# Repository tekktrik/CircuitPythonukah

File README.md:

# CircuitPythonukiah Hardware

Hardware required for the [CircuitPythonukiah project](https://github.com/tekktrik/CircuitPythonukiah)

## Hardware Dependencies
Here are all the things needed: to physically build your very own CircuitPythonukiah:

### Custom Components

The project makes use of two custom parts. The first is the custom PCB that is the heart
of the CircuitPythonukiah.  The second is a base that can be 3D printed, which holds the
PCB upright.  You can find the PCB KiCAD design and fabrication files in the
`electrical/` folder, and you can find both the PCB's STEP file representation, as well
as the STEP and STL files for the base in the `mechanical/` folder.

### Mechanical (Off-The-Shelf)

This project uses the following off-the-shelf mechanical components:

* [Self-Tapping M5 Screw](https://www.mcmaster.com/90380A392/) (x1)
* [M5 Spacer](https://www.mcmaster.com/7298N112/) (x1)

### Electronics (Off-The-Shelf)
This project uses the following off-the-shelf electronic components:

* [QT Py ESP32-S2 Dev Board](https://www.adafruit.com/product/5325) (x1)
* [Piezo Buzzer](https://www.adafruit.com/product/160) (x1)
* [Slide Switch](https://www.digikey.com/en/products/detail/e-switch/EG1218/101726)
* [Super Bright Yellow 5mm LED](https://www.adafruit.com/product/2700>) (x9)
* [100 Ohm Resistor](https://www.digikey.com/en/products/detail/yageo/CFR-25JB-52-100R/246) (x9)
* [Male Header Pins (7 position)](https://www.digikey.com/en/products/detail/harwin-inc/M20-9770746/3727778) (x2)
* [Female Header Pins (7 position)](https://www.digikey.com/en/products/detail/sullins-connector-solutions/PPPC071LFBN-RC/810179) (x2)
* [USB C Receptacle](https://www.digikey.com/en/products/detail/cui-devices/UJC-VP-3-SMT-TR/14310511) (x1)

## Building Hardware

### Fabricating the Custom Components

There isn't necessarily one way to do this, but I can mention how I did it:

I used [JLCPCB](https://jlcpcb.com/) to fabricate my boards, mostly because I knew
they could do blue PCBs and the quote for the weirdly shaped PCB was better than
others I had looked at.

For the base, I used 0.2 mm layer thickness and 20% infill.  I also didn't use supports
when I printed since it came out pretty well without them, and I had a lot of trouble
removing the breakway supports otherwise.  I'm leaving it up to [Hubs](https://www.hubs.com/)
(the printing service I'll be using) to figure that last bit out (not sure I can specify
either).  I decided to print this in black rather than blue since the black made the
board "pop" more.

### Soldering the PCB

This is by far the most labor-intensive step.  Since I didn't plan on this being any
kind of big operation, I decided to hand-solder eerything to the board.  This was fairly
straight forward with the exception of a couple things:

* I would bend each LED so the pins so would be in just about the right place, and then I
  bend the wires again to somewhat lock it in place.  I'd then solder one pin to the board,
  while using one hand to hold the LED and PCB, and the other to use the soldering iron,
  which would allow me to remelt the solder and use my hand to finely position the LED.
* The USB C receptacle was a byproduct of not wanting multiple USB receptacle types
  between the microcontroller and the PCB.  I found that I could do a similar trick as
  the LED and solder one pad to "lock" it, and then use one hand to apply pressure while
  remelting the solder with the other.  Then I just applied solder across the pads, using
  some solder wick to get all the extra.

### Assembling Everything

I used a small hand tool to screw in the self-tapping screw, which helped make sure the board
wasn't rattling too much when everything is assembled.  Don't forget to add the spacer before
tightening everything!

## Licenses and Attribution

The hardware for this project is licensed under the CERN-OHL-S license, and uses components,
both original and modified, with the following licenses:

* Licensed under the Certification Mark License Agreement by the OSHWA:
  * Open Source Hardware Certification Mark
* Licensed under CC-SA by Macklin Chaffee:
  * Gear logo design
* Licensed under CC-BY-SA-4.0 with Design Exception 1.0 by SnapEDA:
  * [EG1218](https://www.snapeda.com/parts/EG1218/E-Switch/view-part/) (modified)
  * [UJC-VP-3-SMT-TR](https://www.snapeda.com/parts/UJC-VP-3-SMT-TR/CUI%20Devices/view-part)

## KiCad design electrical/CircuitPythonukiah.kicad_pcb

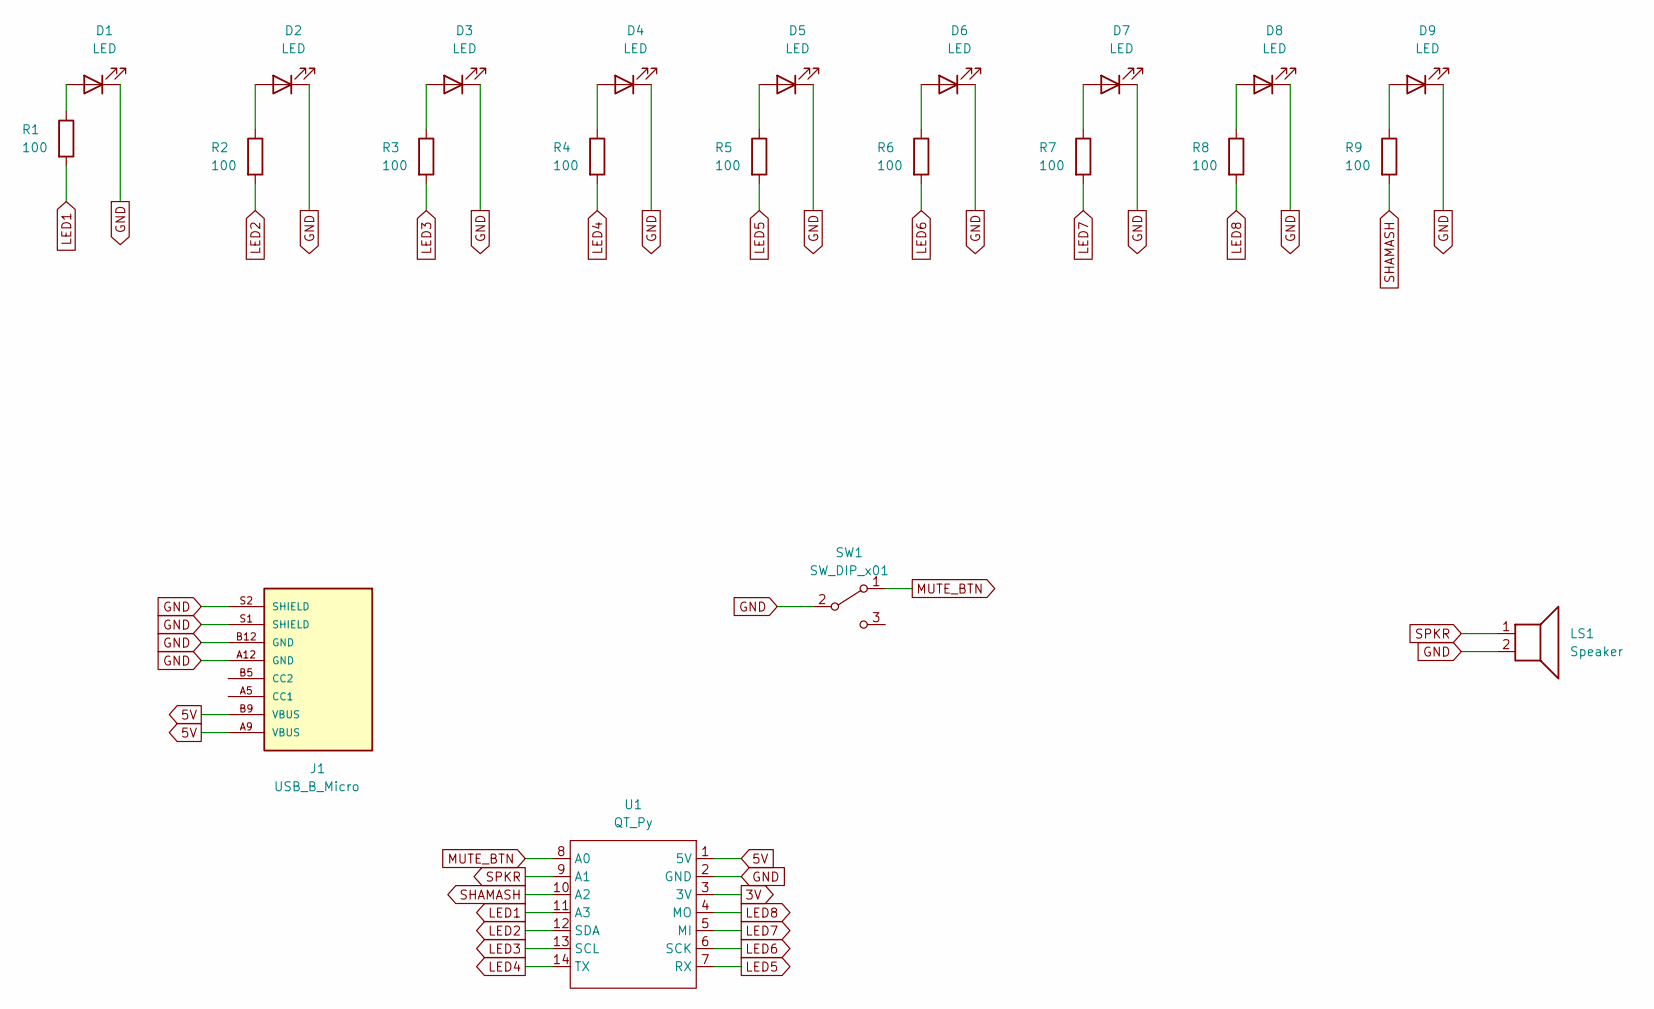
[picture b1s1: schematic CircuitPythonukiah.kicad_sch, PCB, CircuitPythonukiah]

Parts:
D1, D2, D3, D4, D5, D6, D7, D8, D9: LED; LED_D5.0mm_Horizontal_O6.35mm_Z3.0mm
J1: USB_B_Micro; CUI_UJC-VP-3-SMT-TR; PARTREV 1.0
LS1: Speaker; Piezo Buzzer
R1, R2, R3, R4, R5, R6, R7, R8, R9: 100; R_Axial_DIN0207_L6.3mm_D2.5mm_P7.62mm_Horizontal
SW1: SW_DIP_x01; EG1218; PARTREV May 20, 2003
U1: QT_Py; QT Py

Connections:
3V: U1.3 (3V)
5V: J1.A9 (VBUS), J1.B9 (VBUS), U1.1 (5V)
GND: D1.1 (K), D2.1 (K), D3.1 (K), D4.1 (K), D5.1 (K), D6.1 (K), D7.1 (K), D8.1 (K), D9.1 (K), J1.A12 (GND), J1.B12 (GND), J1.S1 (SHIELD), J1.S2 (SHIELD), LS1.2, SW1.2 (B), U1.2 (GND)
LED1: R1.2, U1.11 (A3)
LED2: R2.2, U1.12 (SDA)
LED3: R3.2, U1.13 (SCL)
LED4: R4.2, U1.14 (TX)
LED5: R5.2, U1.7 (RX)
LED6: R6.2, U1.6 (SCK)
LED7: R7.2, U1.5 (MI)
LED8: R8.2, U1.4 (MO)
MUTE_BTN: SW1.1 (A), U1.8 (A0)
unnamed: D1.2 (A), R1.1
unnamed: D2.2 (A), R2.1
unnamed: D3.2 (A), R3.1
unnamed: D4.2 (A), R4.1
unnamed: D5.2 (A), R5.1
unnamed: D6.2 (A), R6.1
unnamed: D7.2 (A), R7.1
unnamed: D8.2 (A), R8.1
unnamed: D9.2 (A), R9.1
SHAMASH: R9.2, U1.10 (A2)
SPKR: LS1.1, U1.9 (A1)

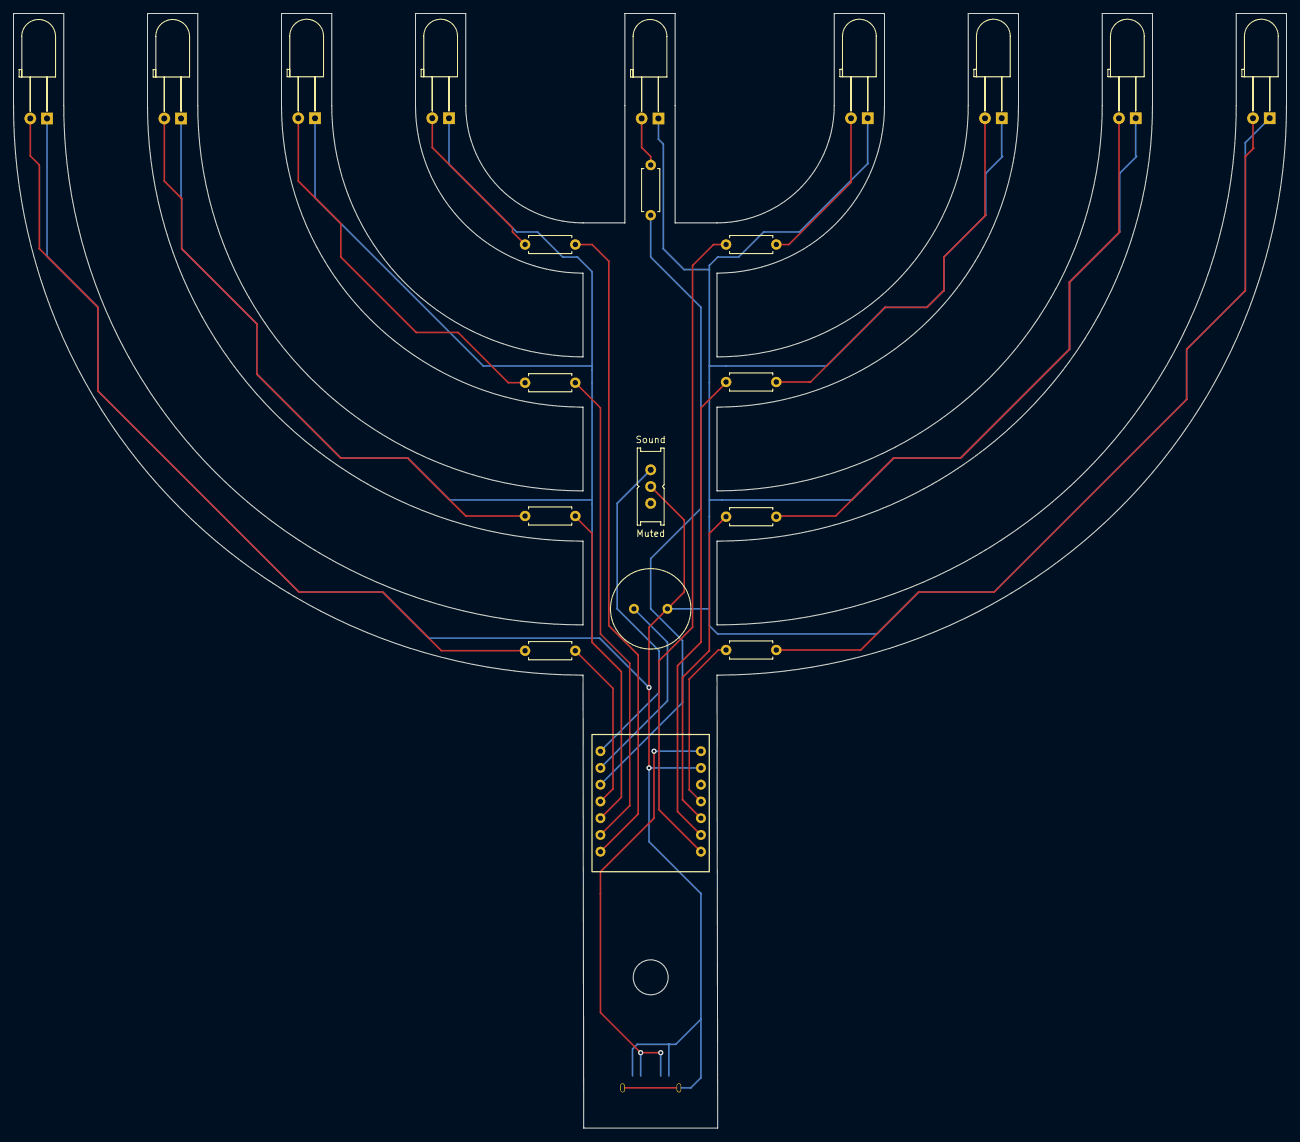
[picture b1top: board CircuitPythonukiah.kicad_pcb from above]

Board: 2 copper layers, 193.0 x 169.0 mm, 23 parts (1 on the bottom side), 22 nets.

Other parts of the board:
M5: MountingHole_5.3mm_M5

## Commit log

2022-04-30 Update project name in README
2022-04-30 Update .gitignore to ignore fabrication folder
2022-04-30 Add project files
2022-04-30 Update .gitignore to ignore backup folder
2022-04-30 Add symbol and footprints
2022-04-30 Add KiCAD files
2022-07-24 Update repo with currnt work
2022-08-14 Move USB-C to back side
2022-08-17 Flip microcontroller for ease of configuring
2022-08-27 Add STEP file output
2022-08-28 Regenerate fabrication outputs
2022-09-16 Change A0 to be pull-up input
2022-09-25 Update fabrication files
2022-10-05 Add preliminary hardware details
2022-10-05 Reorganize files
2022-10-05 Renamed PCB STEP file to pcb.step
2022-10-06 Prepare for pre-commit
2022-10-06 Reformatted STEP files
2022-10-06 Add licensing
2022-10-06 Add CI step for installing dependencies
2022-10-06 Make CI PR parent repo when main is updated
2022-10-06 Remove needs from update CI
2022-10-06 Reformatted per pre-commit
2022-10-06 Add minor fixes to README
2022-10-06 Minor fixes to README
2022-10-06 Fix update CI
2022-10-06 Minor README fixes
2022-10-06 Minor README fix
2022-10-06 Fix typo
2022-10-06 Fix title of README to reference hardware
2022-10-09 Update license to CERN OHL 2.0-S
2022-10-09 Update main license
2022-10-13 Add licenses for SnapEDA components
2022-10-13 Convert attribution to nested list
2022-10-14 Attribute gear logo
2022-10-14 Update PCB drawing info
2022-10-14 Update PCB schematic info
2022-10-14 Add dates as OCT12 to match OSHWA certification
2022-10-14 Add OSHWA mark to PCB
2022-10-14 Add OSHWA mark attribution in README
2022-10-14 Add badges
2022-10-14 Update wording in attribution
2022-10-14 Add CI badge
2022-10-15 Remove output files in preparation for design files
2022-10-15 Add FreeCAD files, ignore output files
2022-10-15 Rename CAD file to Base
2022-10-15 Add README link to parent project repository
2022-12-16 Fix CI badge image link
2022-12-16 Fix image link to point to correct repository
2022-12-20 Updated fab files

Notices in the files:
README.md:
License: CERN-OHL-S-2.0
electrical/CircuitPythonukiah.kicad_pcb:
Licensed under CERN-OHL-S version 2
Copyright Alec Delaney, 2022
